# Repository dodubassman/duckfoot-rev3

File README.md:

# DuckFoot-rev3

Duckfoot is a low profile Corne-inspired split keyboard, powered by Nice!Nano. With a pair of EVQWGD001 roller encoders.

## PCB

Kicab files made with ergogen.

Switches footprint is Kailh Choc V1, supporting [hotswap socket](https://splitkb.com/collections/keyboard-parts/products/kailh-hotswap-sockets?variant=39472161456205) or direct soldering (I wouldnt do that if I were you).

You'll also need:
- MSK12C02 on/off switch
- [Reset micro tactil switch](https://www.aliexpress.com/item/32873382894.html)
- a bunch of smd diodes
- 90mAh batteries. You can chose bigger capacity, but honestly with no LEDs on the board, you won't need more. I chose direct soldering for batteries because JST sockets are to big and a nightmare to wire.

The board is reversible, so one minimal order on PCBWay or JLCPCB gives you 2.5 keyboard and a seconde chance if you suck at soldering.

Reversible means left Nice!Nano has to be soldered upside down. If you're lost, pins are idendified on the printed silk layer of the pcb (at least RAW, GND, RST, VCC).

## Plate and case

Soon.

## Config

### Net matrix
Querty example (promicro)

|      | P2 | P3 | P4 | P7 | P8 | P10 |   
|------|----|----|----|----|----|-----|
| P1   | tab | Q | W | E | R | T |
| P20  | Shift | A | S | D | F | G |
| P19  | Ctrl | Z | X | C | V | B |
| P9   |     |   |  rollclik  | thumb  | thumb |  thumb  |

### ZMK Config example

## Licence

DWTFYWT Public Licence.

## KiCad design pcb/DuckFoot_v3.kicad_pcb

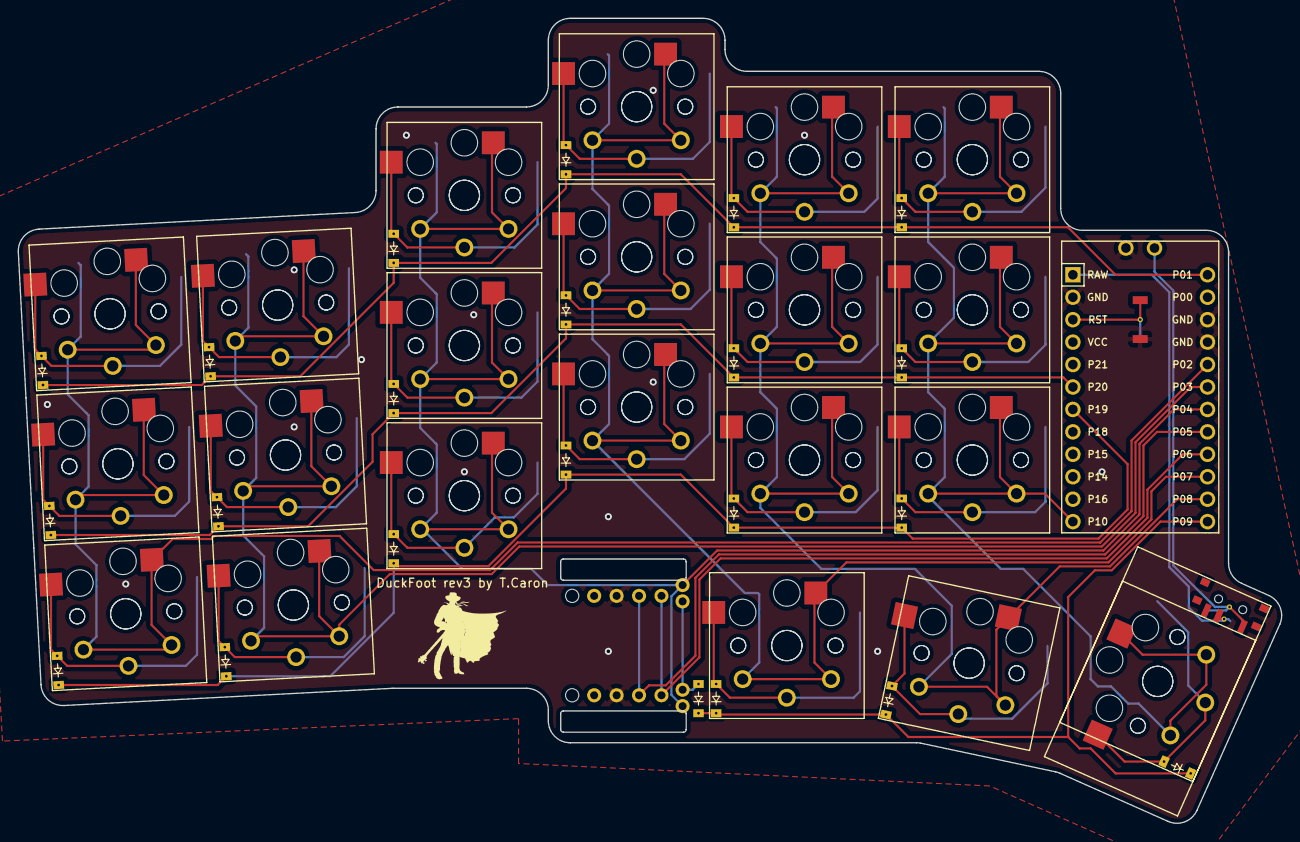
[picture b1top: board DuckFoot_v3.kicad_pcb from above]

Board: 2 copper layers, 143.0 x 91.1 mm, 65 parts (0 on the bottom side), 32 nets.

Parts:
D1, D2, D3, D4, D5, D6, D7, D8, D9, D10, D11, D12, D13, D14, D15, D16, D17, D18, D19, D20, D21, D22: ComboDiode
MCU1: ProMicro
S1, S2, S3, S4, S5, S6, S7, S8, S9, S10, S11, S12, S13, S14, S15, S16, S17, S18, S19, S20, S21, S22, S23, S24, S25, S26, S27, S28, S29, S30, S31, S32, S33, S34, S35, S36, S37, S38, S39, S40, S41, S42: PG1350

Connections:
GND: MCU1.2, MCU1.15, MCU1.16
P1: D3.1, D6.1, D9.1, D12.1, D15.1, D18.1, MCU1.13
P2: MCU1.17, S1.1, S2.1, S3.1, S4.1, S5.1, S6.1
P3: MCU1.18, S7.1, S8.1, S9.1, S10.1, S11.1, S12.1
P4: MCU1.19, S13.1, S14.1, S15.1, S16.1, S17.1, S18.1
P7: MCU1.22, S19.1, S20.1, S21.1, S22.1, S23.1, S24.1, S37.1, S38.1
P8: MCU1.23, S25.1, S26.1, S27.1, S28.1, S29.1, S30.1, S39.1, S40.1
P9: D19.1, D20.1, D21.1, D22.1, MCU1.24
P10: MCU1.12, S31.1, S32.1, S33.1, S34.1, S35.1, S36.1, S41.1, S42.1
P19: D1.1, D4.1, D7.1, D10.1, D13.1, D16.1, MCU1.7
P20: D2.1, D5.1, D8.1, D11.1, D14.1, D17.1, MCU1.6
extra_bottom: D1.2, S1.2, S2.2
extra_home: D2.2, S3.2, S4.2
extra_top: D3.2, S5.2, S6.2
far_bottom: D16.2, S31.2, S32.2
far_home: D17.2, S33.2, S34.2
far_thumb: D21.2, S41.2, S42.2
far_top: D18.2, S35.2, S36.2
home_thumb: D20.2, S39.2, S40.2
index_bottom: D13.2, S25.2, S26.2
index_home: D14.2, S27.2, S28.2
index_top: D15.2, S29.2, S30.2
middle_bottom: D10.2, S19.2, S20.2
middle_home: D11.2, S21.2, S22.2
middle_top: D12.2, S23.2, S24.2
near_thumb: D19.2, S37.2, S38.2
pinky_bottom: D4.2, S7.2, S8.2
pinky_home: D5.2, S9.2, S10.2
pinky_top: D6.2, S11.2, S12.2
ring_bottom: D7.2, S13.2, S14.2
ring_home: D8.2, S15.2, S16.2
ring_top: D9.2, S17.2, S18.2

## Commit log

2022-08-27 Duckfoot rev3 initial commit
2022-08-27 add images
2022-08-27 add n!n warning image
2022-09-07 Update README.md
    fix typo
